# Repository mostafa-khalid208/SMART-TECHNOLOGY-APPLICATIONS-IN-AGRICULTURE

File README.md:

# SMART-TECHNOLOGY-APPLICATIONS-IN-AGRICULTURE

In the ever-changing world of farming, smart agricultural systems have emerged as game-changers, using fancy tech to tackle big challenges like feeding a growing global population while being kind to the planet. This graduation project book is your go-to guide to understand and dive deep into these innovative farming solutions.

[Create & Login Account (Practical application ) ]( https://youtu.be/F7y6CJShDI8 )

We'll take you on a tour of the cool tech behind smart agriculture, from building mobile apps with Flutter to using AI for making smart decisions and managing data in the Cloud. You'll get hands-on with hardware like ESP32 and IoT devices, learning how they collect data and automate tasks on the farm.

[Sensors & Microcontroller ( Practical application ) ]( https://youtu.be/qTxyqkGCsHM )

But it's not all theory—get ready to roll up your sleeves and put these ideas into action. We'll show you how smart irrigation systems work, using sensors and AI to water crops just right. Plus, you'll learn how AI can spot plant diseases early, helping farmers protect their harvests and boost productivity.

[Artificial intelligence (AI) Chat & Image (Practical application ) ]( https://youtu.be/XoeHMlaQuq4 )

[Full in-app AI experience ]( https://youtube.com/shorts/PL40P1889J8 )

We won't just stop at building cool stuff; We'll also talk about how to measure success. We'll look at how these systems increase crop yields, save resources, and make farming more sustainable. And we'll dive into how they're making a real difference in food security and protecting our environment.

But we're not done yet—get ready to peer into the future of farming. We'll explore exciting new technology like 5G, fog computing, and the Internet of Everything, and how they'll shape the farms of tomorrow. And we'll discuss how renewable energy, virtual reality, and more will play a role in making farming even smarter.

[Firebase & FireStore (Practical application ) ]( https://youtu.be/0Hn9pTRTNbc )

By bringing together the latest research and hands-on practices, this project is your ticket to understanding and creating the future of farming. Whether you're a student looking to dive into smart agriculture or a researcher pushing the boundaries of what's possible, this project is your roadmap to a greener, more efficient future in farming.

[Smart Irrigation System (Final practical application of the graduation project ) ]( https://youtube.com/shorts/qQlA1rqxmsU?feature=shared )

[Full mobile app experience ]( https://youtu.be/DmjhwGzqkdA?feature=shared )

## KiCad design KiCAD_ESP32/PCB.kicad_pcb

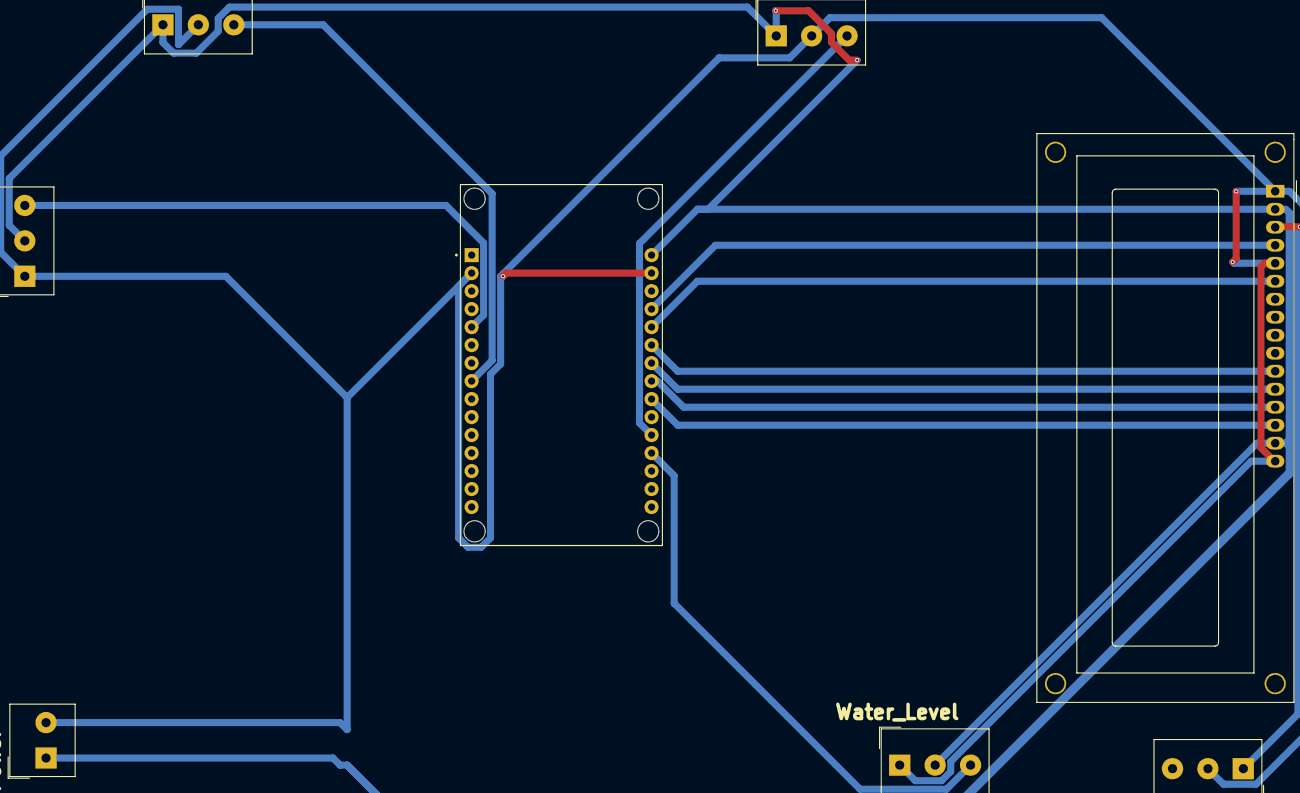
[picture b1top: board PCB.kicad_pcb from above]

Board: 2 copper layers, 8 parts (0 on the bottom side), 13 nets.

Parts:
DHT22: DHT22; Altech_AK100_1x03_P5.00mm
ESP32_WROOM_30-PIN: ESP32-DEVKIT-V1; MODULE_ESP32_DEVKIT_V1
LCD_16*2: WC1602A
Power: Power; Altech_AK100_1x02_P5.00mm
R_Pot: Variable_Resistor; Altech_AK100_1x03_P5.00mm
Relay: Relay; Altech_AK100_1x03_P5.00mm
Soil: Soil; Altech_AK100_1x03_P5.00mm
Water_Level: Water Level; Altech_AK100_1x03_P5.00mm

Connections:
+5V: DHT22.2, ESP32_WROOM_30-PIN.30 (VIN), LCD_16*2.2 (VDD), LCD_16*2.15 (LED(+)), Power.1, Relay.1, Soil.1, Water_Level.2
GND: DHT22.1, ESP32_WROOM_30-PIN.2 (GND), ESP32_WROOM_30-PIN.29 (GND), LCD_16*2.1 (VSS), LCD_16*2.5 (R/W), LCD_16*2.16 (LED(-)), Power.2, R_Pot.2, Relay.2, Soil.2, Water_Level.1
unnamed: ESP32_WROOM_30-PIN.25 (D27), LCD_16*2.11 (D4)
unnamed: ESP32_WROOM_30-PIN.24 (D26), LCD_16*2.12 (D5)
unnamed: ESP32_WROOM_30-PIN.23 (D25), LCD_16*2.13 (D6)
unnamed: ESP32_WROOM_30-PIN.22 (D33), LCD_16*2.14 (D7)
unnamed: ESP32_WROOM_30-PIN.26 (D14), LCD_16*2.6 (E)
unnamed: ESP32_WROOM_30-PIN.27 (D12), LCD_16*2.4 (RS)
unnamed: LCD_16*2.3 (VO), R_Pot.1
unnamed: ESP32_WROOM_30-PIN.20 (D35), Soil.3
unnamed: ESP32_WROOM_30-PIN.8 (D5), Relay.3
unnamed: ESP32_WROOM_30-PIN.19 (D34), Water_Level.3
unnamed: DHT22.3, ESP32_WROOM_30-PIN.5 (D4)

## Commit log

2024-07-01 Create Book PDF & Presentation
2024-07-03 Update
    File
2024-07-03 Create test
2024-07-03 Rename Smart Irrigation System (Final practical application of the graduation project ) 🎓✨(720P_HD).mp4 to Smart Irrigation System (Final practical application of the graduation project ) 🎓✨.mp4
2024-07-03 Rename FlowChart - Copy.pdf to FlowChart.pdf
